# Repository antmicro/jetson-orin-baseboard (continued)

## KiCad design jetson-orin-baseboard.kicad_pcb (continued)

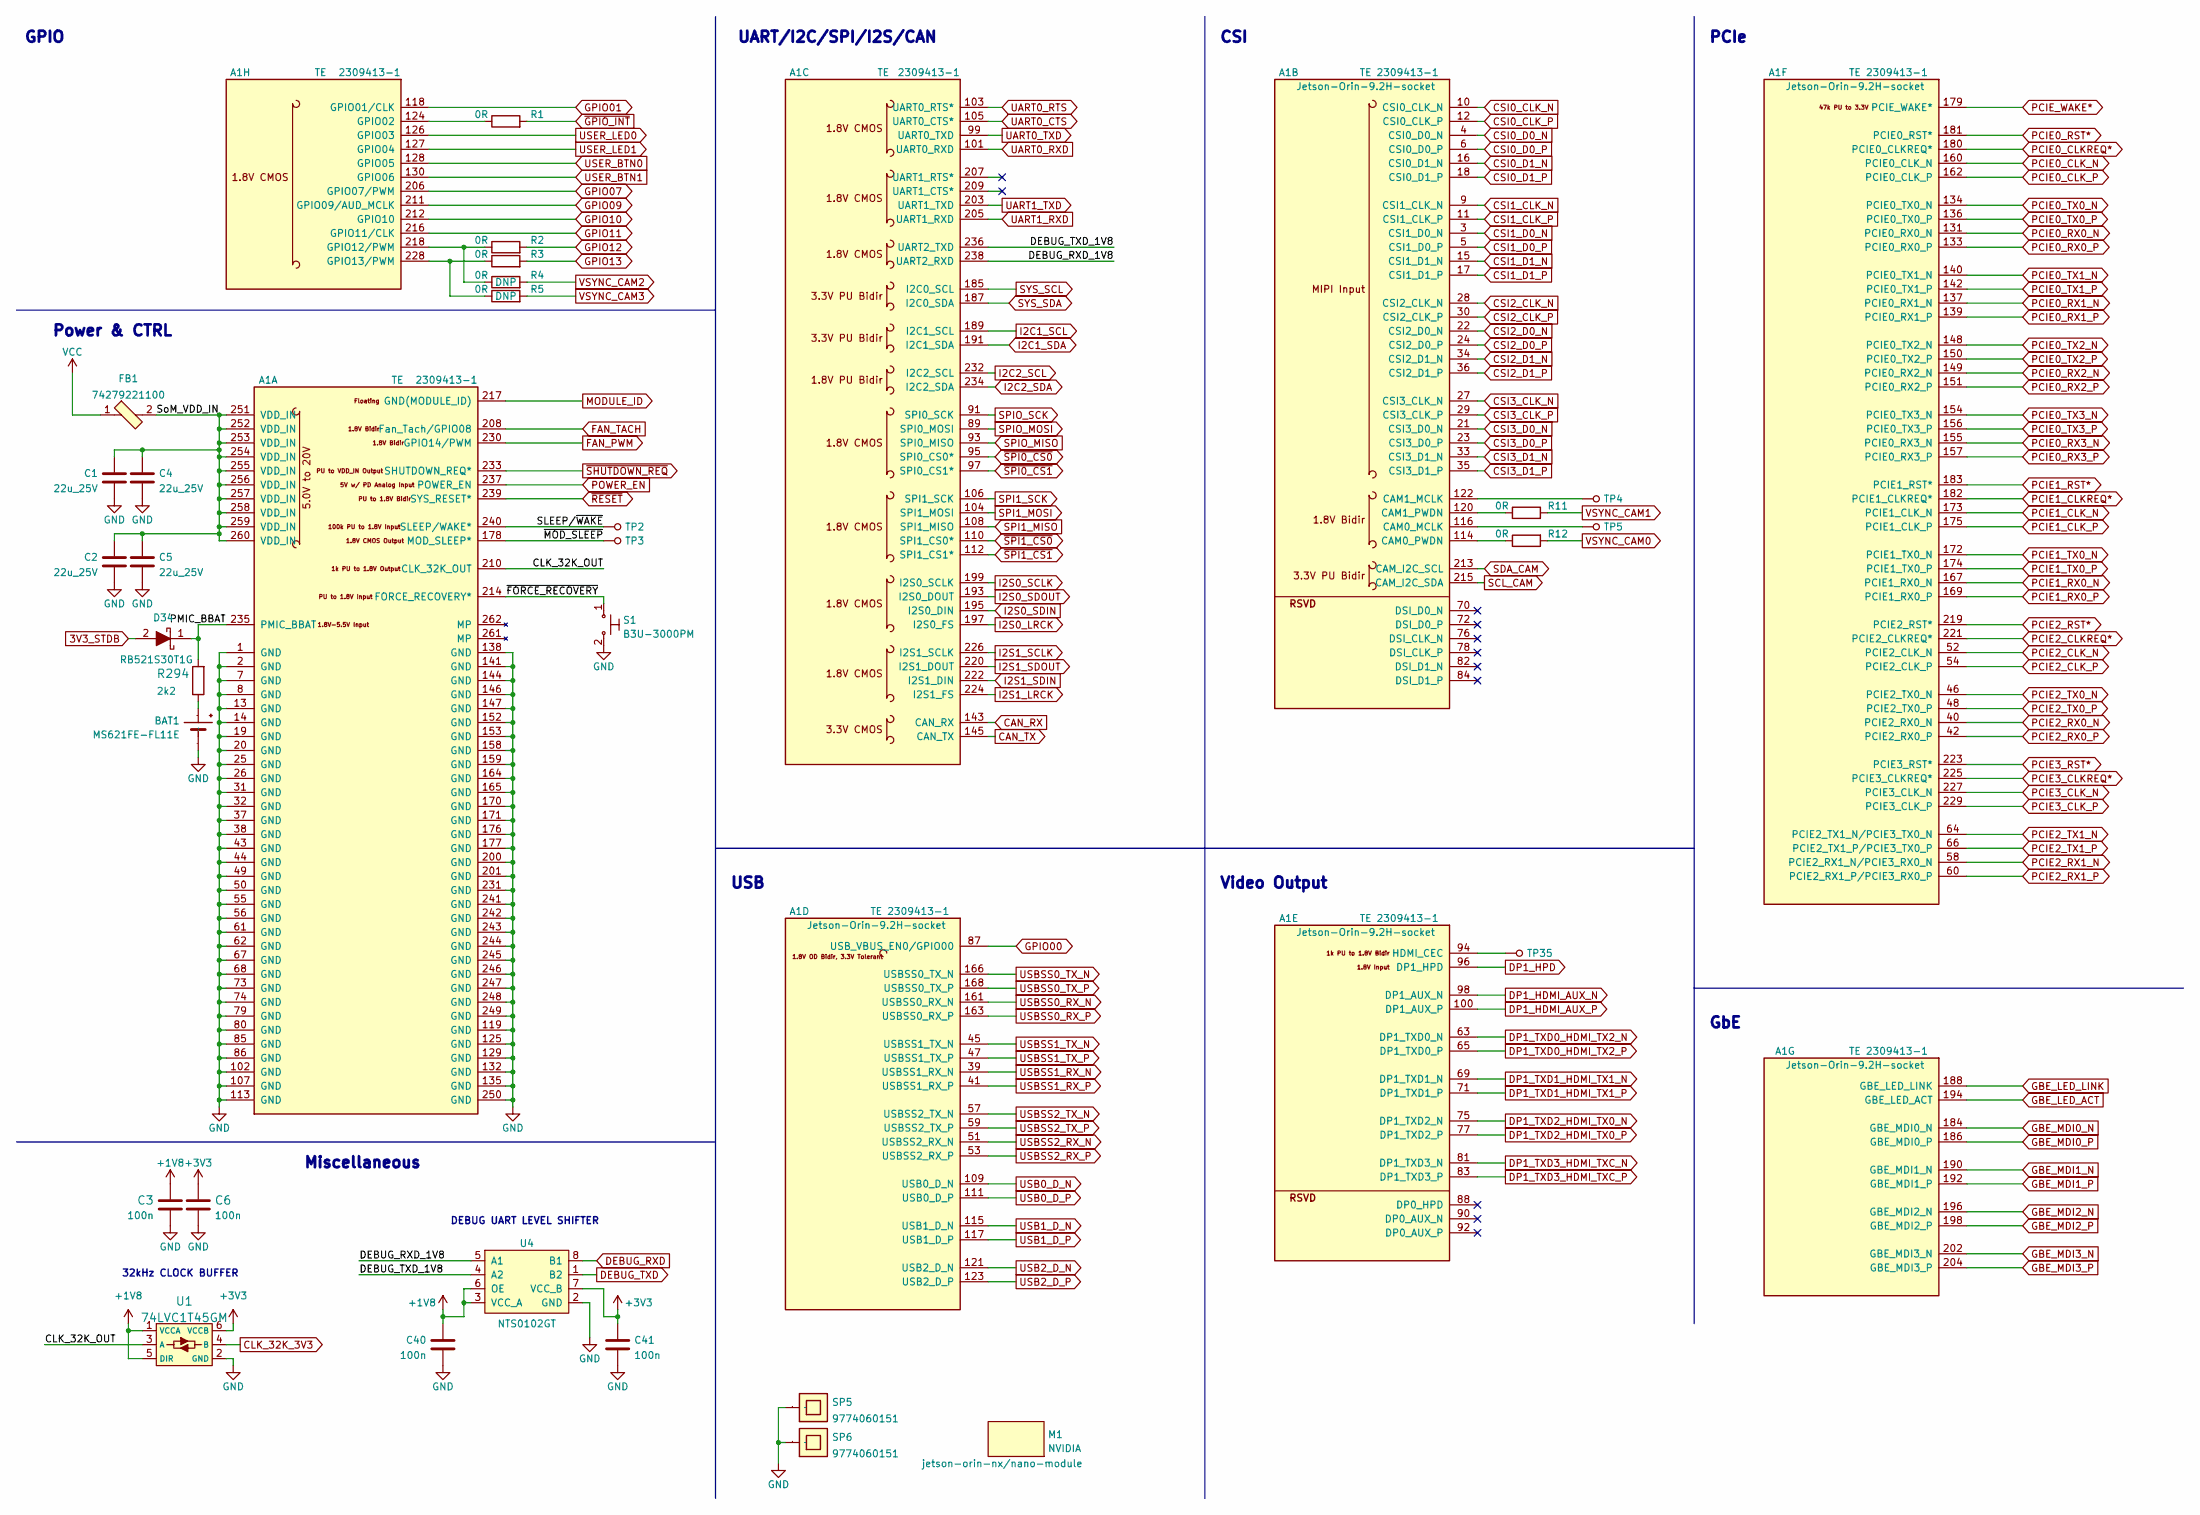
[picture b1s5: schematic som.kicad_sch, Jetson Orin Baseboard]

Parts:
A1: Jetson-Orin-9.2H-socket; TE_2309413; MPN 2309413-1
BAT1: MS621FE-FL11E; MPN MS621FE-FL11E
C1, C2, C4, C5: C_22u_0805_25V; 0805-cap; MPN CL21A226MAYNNNE
C3, C6, C40, C41: C_100n_0402; 0402-cap; MPN GRM155R61H104KE14D
D34: RB521S30T1G; SOD-523; MPN RB521S30T1G
FB1: 74279221100; 1206-res; MPN 74279221100
M1: jetson-orin-nx/nano-module; jetson-orin-nx-nano-module
R1, R2, R3, R4, R5, R11, R12: R_0R_0402; 0402-res; MPN ERJ2GE0R00X
R294: R_2k2_0402; 0402-res; MPN RC0402FR-072K2L
S1: B3U-3000PM; B3U-3000P; MPN B3U-3000PM
SP5, SP6: 9774060151; MPN 9774060151
TP2, TP3, TP4, TP5, TP35: TP_SMD_0_75MM; Testpoint_smd_0_75mm
U1: 74LVC1T45GM; SOT-886; MPN 74LVC1T45GM-Q100X
U4: NTS0102GT; PSON50P100X195X50-8N; MPN NTS0102GT

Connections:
3V3_STDB: D34.2; also elsewhere on the board
+1V8: C3.1, C40.2, U1.1 (VCCA), U1.5 (DIR), U4.3 (VCC_A), U4.6 (OE); also elsewhere on the board
+3V3: C6.1, C41.2, U1.6 (VCCB), U4.7 (VCC_B); also elsewhere on the board
/SoM/CLK_32K_OUT: A1.210 (CLK_32K_OUT), U1.3 (A)
/SoM/DEBUG_RXD_1V8: A1.238 (UART2_RXD), U4.5 (A1)
/SoM/DEBUG_TXD_1V8: A1.236 (UART2_TXD), U4.4 (A2)
/SoM/PMIC_BBAT: A1.235 (PMIC_BBAT), D34.1, R294.2
/SoM/SLEEP/~WAKE: A1.240 (SLEEP/WAKE*), TP2.1
/SoM/SoM_VDD_IN: A1.251 (VDD_IN), A1.252 (VDD_IN), A1.253 (VDD_IN), A1.254 (VDD_IN), A1.255 (VDD_IN), A1.256 (VDD_IN), A1.257 (VDD_IN), A1.258 (VDD_IN), A1.259 (VDD_IN), A1.260 (VDD_IN), C1.1, C2.1, C4.1, C5.1, FB1.2
/SoM/~FORCE_RECOVERY: A1.214 (FORCE_RECOVERY*), S1.1
/SoM/~MOD_SLEEP: A1.178 (MOD_SLEEP*), TP3.1
CAN_RX: A1.143 (CAN_RX); also elsewhere on the board
CAN_TX: A1.145 (CAN_TX); also elsewhere on the board
CLK_32K_3V3: U1.4 (B); also elsewhere on the board
CSI0_CLK_N: A1.10 (CSI0_CLK_N); also elsewhere on the board
CSI0_CLK_P: A1.12 (CSI0_CLK_P); also elsewhere on the board
CSI0_D0_N: A1.4 (CSI0_D0_N); also elsewhere on the board
CSI0_D0_P: A1.6 (CSI0_D0_P); also elsewhere on the board
CSI0_D1_N: A1.16 (CSI0_D1_N); also elsewhere on the board
CSI0_D1_P: A1.18 (CSI0_D1_P); also elsewhere on the board
CSI1_CLK_N: A1.9 (CSI1_CLK_N); also elsewhere on the board
CSI1_CLK_P: A1.11 (CSI1_CLK_P); also elsewhere on the board
CSI1_D0_N: A1.3 (CSI1_D0_N); also elsewhere on the board
CSI1_D0_P: A1.5 (CSI1_D0_P); also elsewhere on the board
CSI1_D1_N: A1.15 (CSI1_D1_N); also elsewhere on the board
CSI1_D1_P: A1.17 (CSI1_D1_P); also elsewhere on the board
CSI2_CLK_N: A1.28 (CSI2_CLK_N); also elsewhere on the board
CSI2_CLK_P: A1.30 (CSI2_CLK_P); also elsewhere on the board
CSI2_D0_N: A1.22 (CSI2_D0_N); also elsewhere on the board
CSI2_D0_P: A1.24 (CSI2_D0_P); also elsewhere on the board
CSI2_D1_N: A1.34 (CSI2_D1_N); also elsewhere on the board
CSI2_D1_P: A1.36 (CSI2_D1_P); also elsewhere on the board
CSI3_CLK_N: A1.27 (CSI3_CLK_N); also elsewhere on the board
CSI3_CLK_P: A1.29 (CSI3_CLK_P); also elsewhere on the board
CSI3_D0_N: A1.21 (CSI3_D0_N); also elsewhere on the board
CSI3_D0_P: A1.23 (CSI3_D0_P); also elsewhere on the board
CSI3_D1_N: A1.33 (CSI3_D1_N); also elsewhere on the board
CSI3_D1_P: A1.35 (CSI3_D1_P); also elsewhere on the board
DEBUG_RXD: U4.8 (B1); also elsewhere on the board
DEBUG_TXD: U4.1 (B2); also elsewhere on the board
DP1_HDMI_AUX_N: A1.98 (DP1_AUX_N); also elsewhere on the board
DP1_HDMI_AUX_P: A1.100 (DP1_AUX_P); also elsewhere on the board
DP1_HPD: A1.96 (DP1_HPD); also elsewhere on the board
DP1_TXD0_HDMI_TX2_N: A1.63 (DP1_TXD0_N); also elsewhere on the board
DP1_TXD0_HDMI_TX2_P: A1.65 (DP1_TXD0_P); also elsewhere on the board
DP1_TXD1_HDMI_TX1_N: A1.69 (DP1_TXD1_N); also elsewhere on the board
DP1_TXD1_HDMI_TX1_P: A1.71 (DP1_TXD1_P); also elsewhere on the board
DP1_TXD2_HDMI_TX0_N: A1.75 (DP1_TXD2_N); also elsewhere on the board
DP1_TXD2_HDMI_TX0_P: A1.77 (DP1_TXD2_P); also elsewhere on the board
DP1_TXD3_HDMI_TXC_N: A1.81 (DP1_TXD3_N); also elsewhere on the board
DP1_TXD3_HDMI_TXC_P: A1.83 (DP1_TXD3_P); also elsewhere on the board
FAN_PWM: A1.230 (GPIO14/PWM); also elsewhere on the board
FAN_TACH: A1.208 (Fan_Tach/GPIO08); also elsewhere on the board
GBE_LED_ACT: A1.194 (GBE_LED_ACT); also elsewhere on the board
GBE_LED_LINK: A1.188 (GBE_LED_LINK); also elsewhere on the board
GBE_MDI0_N: A1.184 (GBE_MDI0_N); also elsewhere on the board
GBE_MDI0_P: A1.186 (GBE_MDI0_P); also elsewhere on the board
GBE_MDI1_N: A1.190 (GBE_MDI1_N); also elsewhere on the board
GBE_MDI1_P: A1.192 (GBE_MDI1_P); also elsewhere on the board
GBE_MDI2_N: A1.196 (GBE_MDI2_N); also elsewhere on the board
GBE_MDI2_P: A1.198 (GBE_MDI2_P); also elsewhere on the board
GBE_MDI3_N: A1.202 (GBE_MDI3_N); also elsewhere on the board
GBE_MDI3_P: A1.204 (GBE_MDI3_P); also elsewhere on the board
GND: A1.1 (GND), A1.2 (GND), A1.7 (GND), A1.8 (GND), A1.13 (GND), A1.14 (GND), A1.19 (GND), A1.20 (GND), A1.25 (GND), A1.26 (GND), A1.31 (GND), A1.32 (GND), A1.37 (GND), A1.38 (GND), A1.43 (GND), A1.44 (GND), A1.49 (GND), A1.50 (GND), A1.55 (GND), A1.56 (GND), A1.61 (GND), A1.62 (GND), A1.67 (GND), A1.68 (GND), A1.73 (GND), A1.74 (GND), A1.79 (GND), A1.80 (GND), A1.85 (GND), A1.86 (GND), A1.102 (GND), A1.107 (GND), A1.113 (GND), A1.119 (GND), A1.125 (GND), A1.129 (GND), A1.132 (GND), A1.135 (GND), A1.138 (GND), A1.141 (GND), A1.144 (GND), A1.146 (GND), A1.147 (GND), A1.152 (GND), A1.153 (GND), A1.158 (GND), A1.159 (GND), A1.164 (GND), A1.165 (GND), A1.170 (GND), A1.171 (GND), A1.176 (GND), A1.177 (GND), A1.200 (GND), A1.201 (GND), A1.231 (GND), A1.241 (GND), A1.242 (GND), A1.243 (GND), A1.244 (GND), A1.245 (GND), A1.246 (GND), A1.247 (GND), A1.248 (GND), A1.249 (GND), A1.250 (GND), BAT1.-, C1.2, C2.2, C3.2, C4.2, C5.2, C6.2, C40.1, C41.1, S1.2, SP5.1, SP6.1, U1.2 (GND), U4.2 (GND); also elsewhere on the board
GPIO00: A1.87 (USB_VBUS_EN0/GPIO00); also elsewhere on the board
GPIO01: A1.118 (GPIO01/CLK); also elsewhere on the board
GPIO07: A1.206 (GPIO07/PWM); also elsewhere on the board
GPIO09: A1.211 (GPIO09/AUD_MCLK); also elsewhere on the board
GPIO10: A1.212 (GPIO10); also elsewhere on the board
GPIO11: A1.216 (GPIO11/CLK); also elsewhere on the board
GPIO12: R2.2; also elsewhere on the board
GPIO13: R3.2; also elsewhere on the board
I2C1_SCL: A1.189 (I2C1_SCL); also elsewhere on the board
I2C1_SDA: A1.191 (I2C1_SDA); also elsewhere on the board
I2C2_SCL: A1.232 (I2C2_SCL); also elsewhere on the board
I2C2_SDA: A1.234 (I2C2_SDA); also elsewhere on the board
I2S0_LRCK: A1.197 (I2S0_FS); also elsewhere on the board
I2S0_SCLK: A1.199 (I2S0_SCLK); also elsewhere on the board
I2S0_SDIN: A1.195 (I2S0_DIN); also elsewhere on the board
I2S0_SDOUT: A1.193 (I2S0_DOUT); also elsewhere on the board
I2S1_LRCK: A1.224 (I2S1_FS); also elsewhere on the board
I2S1_SCLK: A1.226 (I2S1_SCLK); also elsewhere on the board
I2S1_SDIN: A1.222 (I2S1_DIN); also elsewhere on the board
I2S1_SDOUT: A1.220 (I2S1_DOUT); also elsewhere on the board
MODULE_ID: A1.217 (GND(MODULE_ID)); also elsewhere on the board
unnamed: A1.94 (HDMI_CEC), TP35.1
unnamed: A1.114 (CAM0_PWDN), R12.1
unnamed: A1.116 (CAM0_MCLK), TP5.1
unnamed: A1.120 (CAM1_PWDN), R11.1
unnamed: A1.122 (CAM1_MCLK), TP4.1
unnamed: A1.124 (GPIO02), R1.1
unnamed: A1.218 (GPIO12/PWM), R2.1, R4.1
unnamed: A1.228 (GPIO13/PWM), R3.1, R5.1
unnamed: BAT1.+, R294.1
PCIE0_CLKREQ*: A1.180 (PCIE0_CLKREQ*); also elsewhere on the board
PCIE0_CLK_N: A1.160 (PCIE0_CLK_N); also elsewhere on the board
PCIE0_CLK_P: A1.162 (PCIE0_CLK_P); also elsewhere on the board
PCIE0_RST*: A1.181 (PCIE0_RST*); also elsewhere on the board
PCIE0_RX0_N: A1.131 (PCIE0_RX0_N); also elsewhere on the board
PCIE0_RX0_P: A1.133 (PCIE0_RX0_P); also elsewhere on the board
PCIE0_RX1_N: A1.137 (PCIE0_RX1_N); also elsewhere on the board
PCIE0_RX1_P: A1.139 (PCIE0_RX1_P); also elsewhere on the board
PCIE0_RX2_N: A1.149 (PCIE0_RX2_N); also elsewhere on the board
PCIE0_RX2_P: A1.151 (PCIE0_RX2_P); also elsewhere on the board
PCIE0_RX3_N: A1.155 (PCIE0_RX3_N); also elsewhere on the board
PCIE0_RX3_P: A1.157 (PCIE0_RX3_P); also elsewhere on the board
PCIE0_TX0_N: A1.134 (PCIE0_TX0_N); also elsewhere on the board
PCIE0_TX0_P: A1.136 (PCIE0_TX0_P); also elsewhere on the board
PCIE0_TX1_N: A1.140 (PCIE0_TX1_N); also elsewhere on the board
PCIE0_TX1_P: A1.142 (PCIE0_TX1_P); also elsewhere on the board
PCIE0_TX2_N: A1.148 (PCIE0_TX2_N); also elsewhere on the board
PCIE0_TX2_P: A1.150 (PCIE0_TX2_P); also elsewhere on the board
PCIE0_TX3_N: A1.154 (PCIE0_TX3_N); also elsewhere on the board
PCIE0_TX3_P: A1.156 (PCIE0_TX3_P); also elsewhere on the board
PCIE1_CLKREQ*: A1.182 (PCIE1_CLKREQ*); also elsewhere on the board
PCIE1_CLK_N: A1.173 (PCIE1_CLK_N); also elsewhere on the board
PCIE1_CLK_P: A1.175 (PCIE1_CLK_P); also elsewhere on the board
PCIE1_RST*: A1.183 (PCIE1_RST*); also elsewhere on the board
PCIE1_RX0_N: A1.167 (PCIE1_RX0_N); also elsewhere on the board
PCIE1_RX0_P: A1.169 (PCIE1_RX0_P); also elsewhere on the board
PCIE1_TX0_N: A1.172 (PCIE1_TX0_N); also elsewhere on the board
PCIE1_TX0_P: A1.174 (PCIE1_TX0_P); also elsewhere on the board
PCIE2_CLKREQ*: A1.221 (PCIE2_CLKREQ*); also elsewhere on the board
PCIE2_CLK_N: A1.52 (PCIE2_CLK_N); also elsewhere on the board
PCIE2_CLK_P: A1.54 (PCIE2_CLK_P); also elsewhere on the board
PCIE2_RST*: A1.219 (PCIE2_RST*); also elsewhere on the board
PCIE2_RX0_N: A1.40 (PCIE2_RX0_N); also elsewhere on the board
PCIE2_RX0_P: A1.42 (PCIE2_RX0_P); also elsewhere on the board
PCIE2_RX1_N: A1.58 (PCIE2_RX1_N/PCIE3_RX0_N); also elsewhere on the board
PCIE2_RX1_P: A1.60 (PCIE2_RX1_P/PCIE3_RX0_P); also elsewhere on the board
PCIE2_TX0_N: A1.46 (PCIE2_TX0_N); also elsewhere on the board
PCIE2_TX0_P: A1.48 (PCIE2_TX0_P); also elsewhere on the board
PCIE2_TX1_N: A1.64 (PCIE2_TX1_N/PCIE3_TX0_N); also elsewhere on the board
PCIE2_TX1_P: A1.66 (PCIE2_TX1_P/PCIE3_TX0_P); also elsewhere on the board
PCIE3_CLKREQ*: A1.225 (PCIE3_CLKREQ*); also elsewhere on the board
PCIE3_CLK_N: A1.227 (PCIE3_CLK_N); also elsewhere on the board
PCIE3_CLK_P: A1.229 (PCIE3_CLK_P); also elsewhere on the board
PCIE3_RST*: A1.223 (PCIE3_RST*)
PCIE_WAKE*: A1.179 (PCIE_WAKE*); also elsewhere on the board
POWER_EN: A1.237 (POWER_EN); also elsewhere on the board
SCL_CAM: A1.215 (CAM_I2C_SDA); also elsewhere on the board
SDA_CAM: A1.213 (CAM_I2C_SCL); also elsewhere on the board
SPI1_MISO: A1.108 (SPI1_MISO); also elsewhere on the board
SPI1_MOSI: A1.104 (SPI1_MOSI); also elsewhere on the board
SPI1_SCK: A1.106 (SPI1_SCK); also elsewhere on the board
SPIO_MISO: A1.93 (SPI0_MISO); also elsewhere on the board
SPIO_MOSI: A1.89 (SPI0_MOSI); also elsewhere on the board
SPIO_SCK: A1.91 (SPI0_SCK); also elsewhere on the board
SYS_SCL: A1.185 (I2C0_SCL); also elsewhere on the board
SYS_SDA: A1.187 (I2C0_SDA); also elsewhere on the board
UART0_CTS: A1.105 (UART0_CTS*); also elsewhere on the board
UART0_RTS: A1.103 (UART0_RTS*); also elsewhere on the board
UART0_RXD: A1.101 (UART0_RXD); also elsewhere on the board
UART0_TXD: A1.99 (UART0_TXD); also elsewhere on the board
UART1_RXD: A1.205 (UART1_RXD); also elsewhere on the board
UART1_TXD: A1.203 (UART1_TXD); also elsewhere on the board
USB0_D_N: A1.109 (USB0_D_N); also elsewhere on the board
USB0_D_P: A1.111 (USB0_D_P); also elsewhere on the board
USB1_D_N: A1.115 (USB1_D_N); also elsewhere on the board
USB1_D_P: A1.117 (USB1_D_P); also elsewhere on the board
USB2_D_N: A1.121 (USB2_D_N); also elsewhere on the board
USB2_D_P: A1.123 (USB2_D_P); also elsewhere on the board
USBSS0_RX_N: A1.161 (USBSS0_RX_N); also elsewhere on the board
USBSS0_RX_P: A1.163 (USBSS0_RX_P); also elsewhere on the board
USBSS0_TX_N: A1.166 (USBSS0_TX_N); also elsewhere on the board
USBSS0_TX_P: A1.168 (USBSS0_TX_P); also elsewhere on the board
USBSS1_RX_N: A1.39 (USBSS1_RX_N); also elsewhere on the board
USBSS1_RX_P: A1.41 (USBSS1_RX_P); also elsewhere on the board
USBSS1_TX_N: A1.45 (USBSS1_TX_N); also elsewhere on the board
USBSS1_TX_P: A1.47 (USBSS1_TX_P); also elsewhere on the board
USBSS2_RX_N: A1.51 (USBSS2_RX_N); also elsewhere on the board
USBSS2_RX_P: A1.53 (USBSS2_RX_P); also elsewhere on the board
USBSS2_TX_N: A1.57 (USBSS2_TX_N); also elsewhere on the board
USBSS2_TX_P: A1.59 (USBSS2_TX_P); also elsewhere on the board
USER_BTN0: A1.128 (GPIO05); also elsewhere on the board
USER_BTN1: A1.130 (GPIO06); also elsewhere on the board
USER_LED0: A1.126 (GPIO03); also elsewhere on the board
USER_LED1: A1.127 (GPIO04); also elsewhere on the board
VCC: FB1.1; also elsewhere on the board
VSYNC_CAM0: R12.2; also elsewhere on the board
VSYNC_CAM1: R11.2; also elsewhere on the board
VSYNC_CAM2: R4.2; also elsewhere on the board
VSYNC_CAM3: R5.2; also elsewhere on the board
~GPIO_INT: R1.2; also elsewhere on the board
~RESET: A1.239 (SYS_RESET*); also elsewhere on the board
~SHUTDOWN_REQ: A1.233 (SHUTDOWN_REQ*); also elsewhere on the board
~SPI0_CS0: A1.95 (SPI0_CS0*); also elsewhere on the board
~SPI0_CS1: A1.97 (SPI0_CS1*); also elsewhere on the board
~SPI1_CS0: A1.110 (SPI1_CS0*); also elsewhere on the board
~SPI1_CS1: A1.112 (SPI1_CS1*); also elsewhere on the board

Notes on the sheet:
DEBUG UART LEVEL SHIFTER
CSI
32kHz CLOCK BUFFER
Video Output
Power & CTRL
UART/I2C/SPI/I2S/CAN
PCIe
GbE
USB
GPIO
Miscellaneous

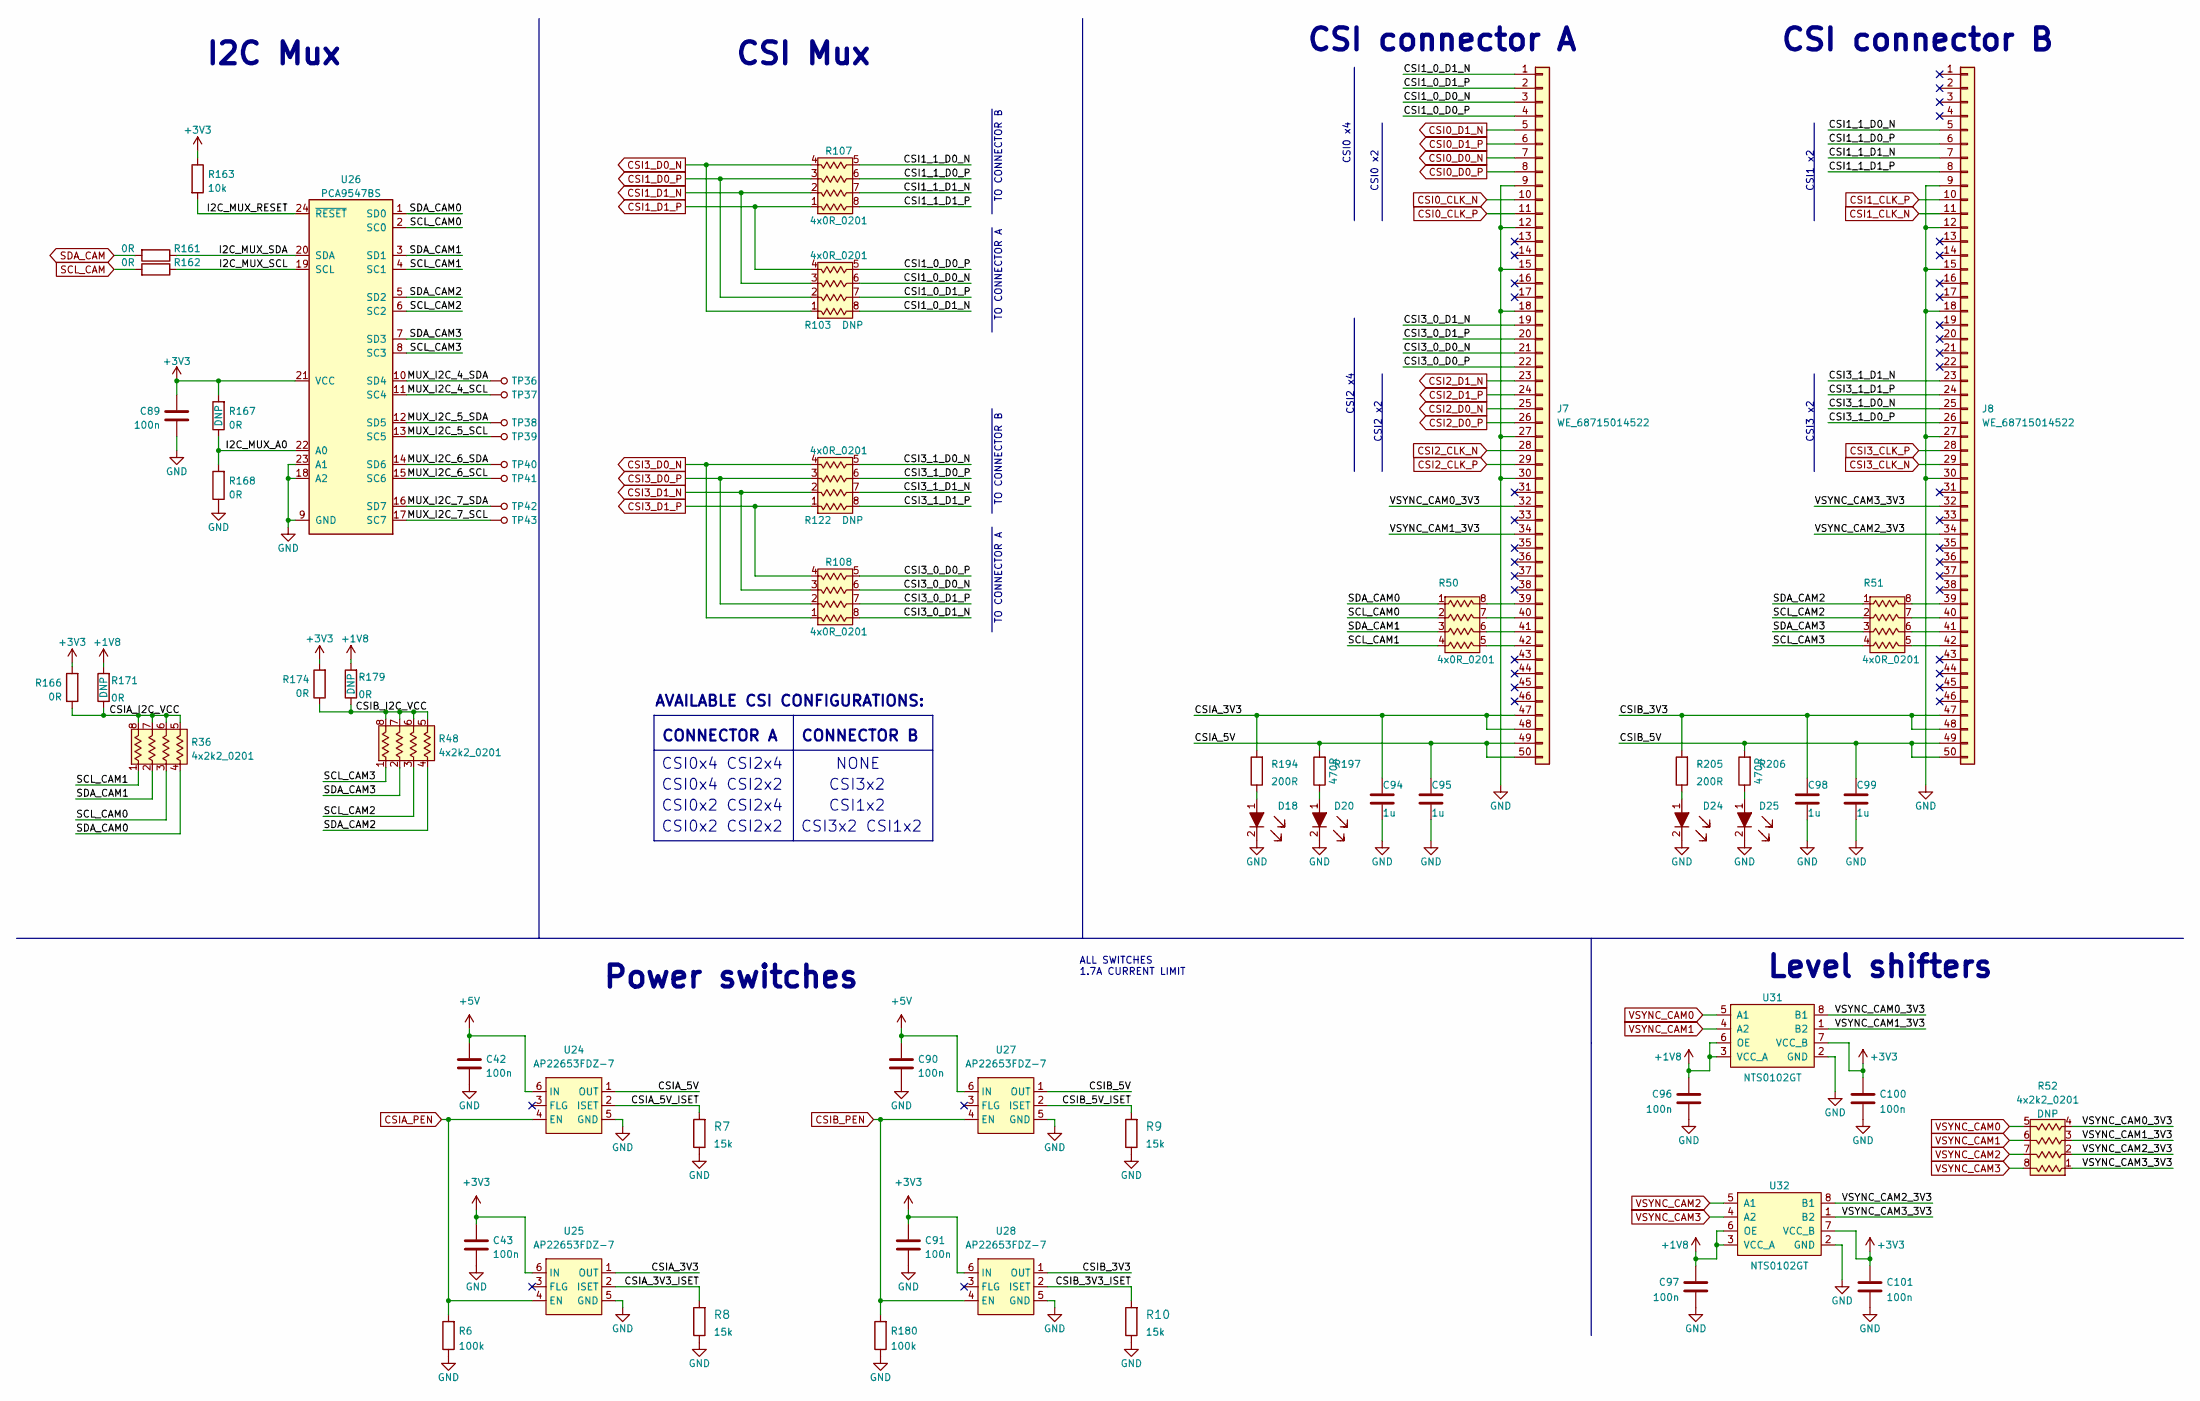
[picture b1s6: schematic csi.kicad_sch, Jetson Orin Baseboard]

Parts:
C42, C43, C89, C90, C91, C96, C97, C100, C101: C_100n_0402; 0402-cap; MPN GRM155R61H104KE14D
C94, C95, C98, C99: C_1u_0402; 0402-cap; MPN C1005X6S1A105K050BC
D18, D20, D24, D25: LTST-C190GKT; LED_0603; MPN LTST-C190GKT
J7, J8: WE_68715014522; MPN 68715014522
R6, R180: R_100k_0402; 0402-res; MPN CRCW0402100KFKEDHP
R7, R8, R9, R10: R_15k_0402; 0402-res; MPN SFR01MZPF1502
R36, R48, R52: 4x2k2_0201_array; EXB18V; MPN EXB-18V222JX
R50, R51, R103, R107, R108, R122: 4x0R_0201_array; EXB18V; MPN EXB-18VR000X
R161, R162, R166, R167, R168, R171, R174, R179: R_0R_0402; 0402-res; MPN ERJ2GE0R00X
R163: R_10k_0402; 0402-res; MPN CRCW040210K0FKEDHP
R194, R205: R_200R_0603; 0603-res; MPN ERJ-UP3F2000V
R197, R206: R_470R_0402; 0402-res; MPN CRCW0402470RFKED
TP36, TP37, TP38, TP39, TP40, TP41, TP42, TP43: TP_SMD_0_75MM; Testpoint_smd_0_75mm
U24, U25, U27, U28: AP22653FDZ-7; DFN-6-1EP_2x2mm_P0.65mm_EP1x1.6mm; MPN AP22653FDZ-7
U26: PCA9547BS; VQFN-24; MPN PCA9547BS,118
U31, U32: NTS0102GT; PSON50P100X195X50-8N; MPN NTS0102GT

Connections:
+1V8: C96.2, C97.2, R171.2, R179.2, U31.3 (VCC_A), U31.6 (OE), U32.3 (VCC_A), U32.6 (OE); also elsewhere on the board
+3V3: C43.1, C89.1, C91.1, C100.2, C101.2, R163.1, R166.2, R167.2, R174.2, U25.6 (IN), U26.21 (VCC), U28.6 (IN), U31.7 (VCC_B), U32.7 (VCC_B); also elsewhere on the board
+5V: C42.1, C90.1, U24.6 (IN), U27.6 (IN); also elsewhere on the board
/CSI/CSI1_0_D0_N: J7.3, R103.6
/CSI/CSI1_0_D0_P: J7.4, R103.5
/CSI/CSI1_0_D1_N: J7.1, R103.8
/CSI/CSI1_0_D1_P: J7.2, R103.7
/CSI/CSI1_1_D0_N: J8.5, R107.5
/CSI/CSI1_1_D0_P: J8.6, R107.6
/CSI/CSI1_1_D1_N: J8.7, R107.7
/CSI/CSI1_1_D1_P: J8.8, R107.8
/CSI/CSI3_0_D0_N: J7.21, R108.6
/CSI/CSI3_0_D0_P: J7.22, R108.5
/CSI/CSI3_0_D1_N: J7.19, R108.8
/CSI/CSI3_0_D1_P: J7.20, R108.7
/CSI/CSI3_1_D0_N: J8.25, R122.5
/CSI/CSI3_1_D0_P: J8.26, R122.6
/CSI/CSI3_1_D1_N: J8.23, R122.7
/CSI/CSI3_1_D1_P: J8.24, R122.8
/CSI/CSIA_3V3: C94.1, J7.47, J7.48, R194.2, U25.1 (OUT)
/CSI/CSIA_3V3_ISET: R8.2, U25.2 (ISET)
/CSI/CSIA_5V: C95.1, J7.49, J7.50, R197.2, U24.1 (OUT)
/CSI/CSIA_5V_ISET: R7.2, U24.2 (ISET)
/CSI/CSIA_I2C_VCC: R36.5, R36.6, R36.7, R36.8, R166.1, R171.1
/CSI/CSIB_3V3: C98.1, J8.47, J8.48, R205.2, U28.1 (OUT)
/CSI/CSIB_3V3_ISET: R10.2, U28.2 (ISET)
/CSI/CSIB_5V: C99.1, J8.49, J8.50, R206.2, U27.1 (OUT)
/CSI/CSIB_5V_ISET: R9.2, U27.2 (ISET)
/CSI/CSIB_I2C_VCC: R48.5, R48.6, R48.7, R48.8, R174.1, R179.1
/CSI/I2C_MUX_A0: R167.1, R168.2, U26.22 (A0)
/CSI/I2C_MUX_RESET: R163.2, U26.24 (~RESET)
/CSI/I2C_MUX_SCL: R162.1, U26.19 (SCL)
/CSI/I2C_MUX_SDA: R161.1, U26.20 (SDA)
/CSI/MUX_I2C_4_SCL: TP37.1, U26.11 (SC4)
/CSI/MUX_I2C_4_SDA: TP36.1, U26.10 (SD4)
/CSI/MUX_I2C_5_SCL: TP39.1, U26.13 (SC5)
/CSI/MUX_I2C_5_SDA: TP38.1, U26.12 (SD5)
/CSI/MUX_I2C_6_SCL: TP41.1, U26.15 (SC6)
/CSI/MUX_I2C_6_SDA: TP40.1, U26.14 (SD6)
/CSI/MUX_I2C_7_SCL: TP43.1, U26.17 (SC7)
/CSI/MUX_I2C_7_SDA: TP42.1, U26.16 (SD7)
/CSI/SCL_CAM0: R36.3, R50.2, U26.2 (SC0)
/CSI/SCL_CAM1: R36.1, R50.4, U26.4 (SC1)
/CSI/SCL_CAM2: R48.3, R51.2, U26.6 (SC2)
/CSI/SCL_CAM3: R48.1, R51.4, U26.8 (SC3)
/CSI/SDA_CAM0: R36.4, R50.1, U26.1 (SD0)
/CSI/SDA_CAM1: R36.2, R50.3, U26.3 (SD1)
/CSI/SDA_CAM2: R48.4, R51.1, U26.5 (SD2)
/CSI/SDA_CAM3: R48.2, R51.3, U26.7 (SD3)
/CSI/VSYNC_CAM0_3V3: J7.32, R52.4, U31.8 (B1)
/CSI/VSYNC_CAM1_3V3: J7.34, R52.3, U31.1 (B2)
/CSI/VSYNC_CAM2_3V3: J8.34, R52.2, U32.8 (B1)
/CSI/VSYNC_CAM3_3V3: J8.32, R52.1, U32.1 (B2)
CSI0_CLK_N: J7.10; also elsewhere on the board
CSI0_CLK_P: J7.11; also elsewhere on the board
CSI0_D0_N: J7.7; also elsewhere on the board
CSI0_D0_P: J7.8; also elsewhere on the board
CSI0_D1_N: J7.5; also elsewhere on the board
CSI0_D1_P: J7.6; also elsewhere on the board
CSI1_CLK_N: J8.11; also elsewhere on the board
CSI1_CLK_P: J8.10; also elsewhere on the board
CSI1_D0_N: R103.1, R107.4; also elsewhere on the board
CSI1_D0_P: R103.2, R107.3; also elsewhere on the board
CSI1_D1_N: R103.3, R107.2; also elsewhere on the board
CSI1_D1_P: R103.4, R107.1; also elsewhere on the board
CSI2_CLK_N: J7.28; also elsewhere on the board
CSI2_CLK_P: J7.29; also elsewhere on the board
CSI2_D0_N: J7.25; also elsewhere on the board
CSI2_D0_P: J7.26; also elsewhere on the board
CSI2_D1_N: J7.23; also elsewhere on the board
CSI2_D1_P: J7.24; also elsewhere on the board
CSI3_CLK_N: J8.29; also elsewhere on the board
CSI3_CLK_P: J8.28; also elsewhere on the board
CSI3_D0_N: R108.1, R122.4; also elsewhere on the board
CSI3_D0_P: R108.2, R122.3; also elsewhere on the board
CSI3_D1_N: R108.3, R122.2; also elsewhere on the board
CSI3_D1_P: R108.4, R122.1; also elsewhere on the board
CSIA_PEN: R6.2, U24.4 (EN), U25.4 (EN); also elsewhere on the board
CSIB_PEN: R180.2, U27.4 (EN), U28.4 (EN); also elsewhere on the board
GND: C42.2, C43.2, C89.2, C90.2, C91.2, C94.2, C95.2, C96.1, C97.1, C98.2, C99.2, C100.1, C101.1, D18.2, D20.2, D24.2, D25.2, J7.9, J7.12, J7.15, J7.18, J7.27, J7.30, J8.9, J8.12, J8.15, J8.18, J8.27, J8.30, R6.1, R7.1, R8.1, R9.1, R10.1, R168.1, R180.1, U24.5 (GND), U25.5 (GND), U26.9 (GND), U26.18 (A2), U26.23 (A1), U27.5 (GND), U28.5 (GND), U31.2 (GND), U32.2 (GND); also elsewhere on the board
unnamed: D18.1, R194.1
unnamed: D20.1, R197.1
unnamed: D24.1, R205.1
unnamed: D25.1, R206.1
unnamed: J7.39, R50.8
unnamed: J7.40, R50.7
unnamed: J7.41, R50.6
unnamed: J7.42, R50.5
unnamed: J8.39, R51.8
unnamed: J8.40, R51.7
unnamed: J8.41, R51.6
unnamed: J8.42, R51.5
SCL_CAM: R162.2; also elsewhere on the board
SDA_CAM: R161.2; also elsewhere on the board
VSYNC_CAM0: R52.5, U31.5 (A1); also elsewhere on the board
VSYNC_CAM1: R52.6, U31.4 (A2); also elsewhere on the board
VSYNC_CAM2: R52.7, U32.5 (A1); also elsewhere on the board
VSYNC_CAM3: R52.8, U32.4 (A2); also elsewhere on the board

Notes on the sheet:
CONNECTOR B
CSI2 x2
CSI0x2 CSI2x2
CONNECTOR A
CSI1x2
NONE
CSI3x2
TO CONNECTOR A
CSI3x2 CSI1x2
CSI0 x2
CSI3 x2
TO CONNECTOR B
CSI0x4 CSI2x2
Power switches
CSI2 x4
CSI0x4 CSI2x4
CSI1 x2
AVAILABLE CSI CONFIGURATIONS:
CSI Mux
CSI connector A
CSI0x2 CSI2x4
CSI0 x4
I2C Mux
CSI connector B
ALL SWITCHES 1.7A CURRENT LIMIT
Level shifters
